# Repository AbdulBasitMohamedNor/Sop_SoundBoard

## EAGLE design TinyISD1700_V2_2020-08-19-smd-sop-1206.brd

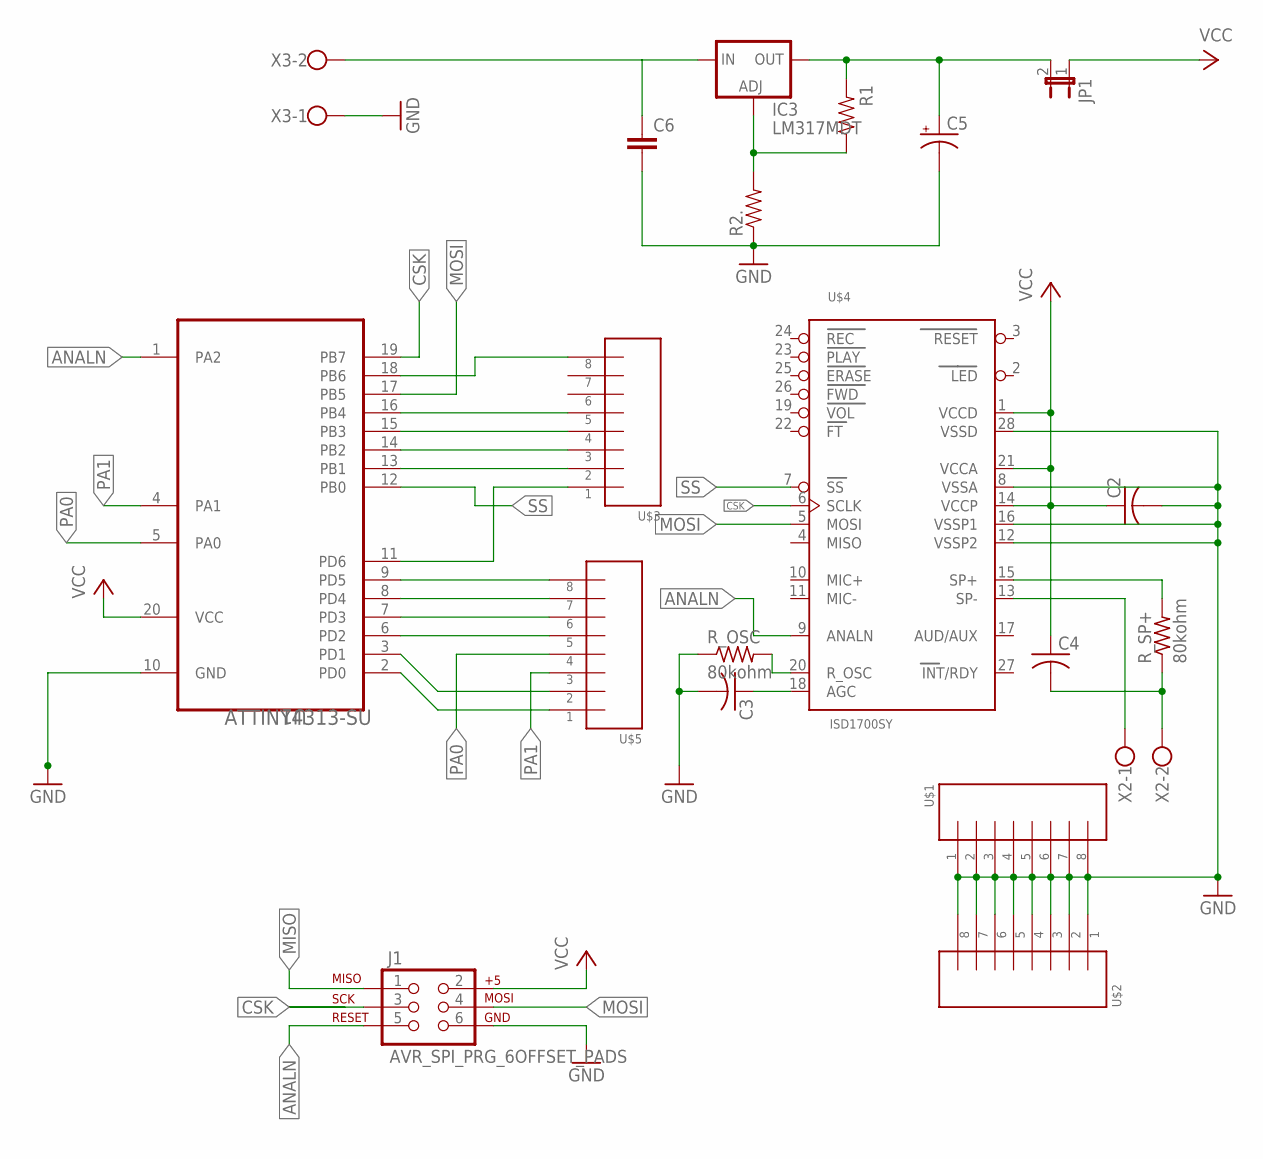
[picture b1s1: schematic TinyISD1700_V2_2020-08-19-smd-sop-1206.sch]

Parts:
C2, C3, C4: C-US050-030X075; C050-030X075
C5: CAP_POL1206; EIA3216
C6: CAP0805; 0805
IC3: LM317MDT; DPACK
J1: AVR_SPI_PRG_6OFFSET_PADS; 2X3_OFFSET
JP1: JP1E; JP1
R1, R2.: RESISTOR; 0805
R_OSC: 80kohm; 0204V
R_SP+: 80kohm; 0204V
U1: ATTINY4313-SU; SOIC127P1032X265-20N
U$1, U$2, U$3, U$5: 8PIN_HEADER; MPN YSDKS128E10
U$4: ISD1700SY; SO28W
X2, X3: W237-102

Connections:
ANALN: J1.5, U1.1 (PA2), U$4.9 (ANALN)
CSK: J1.3, U1.19 (PB7), U$4.6 (SCLK)
GND: C2.2, C3.2, C5.C (-), C6.2, J1.6, R2..1, R_OSC.1, U1.10 (GND), U$1.P$1, U$1.P$2, U$1.P$3, U$1.P$4, U$1.P$5, U$1.P$6, U$1.P$7, U$1.P$8, U$2.P$1, U$2.P$2, U$2.P$3, U$2.P$4, U$2.P$5, U$2.P$6, U$2.P$7, U$2.P$8, U$4.8 (VSSA), U$4.12 (VSSP2), U$4.16 (VSSP1), U$4.28 (VSSD), X3.1
MISO: J1.1
MOSI: J1.4, U1.17 (PB5), U$4.5 (MOSI)
unnamed: R_OSC.2, U$4.20 (R_OSC)
unnamed: U1.13 (PB1), U$3.P$2
unnamed: U1.14 (PB2), U$3.P$3
unnamed: C4.2, R_SP+.1, X2.2
unnamed: C3.1, U$4.18 (AGC)
unnamed: U$4.13 (SP-), X2.1
unnamed: R_SP+.2, U$4.15 (SP+)
unnamed: U1.15 (PB3), U$3.P$4
unnamed: U1.11 (PD6), U$3.P$1
unnamed: U1.9 (PD5), U$5.P$8
unnamed: U1.8 (PD4), U$5.P$7
unnamed: U1.7 (PD3), U$5.P$6
unnamed: U1.6 (PD2), U$5.P$5
unnamed: U1.3 (PD1), U$5.P$2
unnamed: U1.2 (PD0), U$5.P$1
unnamed: C5.A (+), IC3.4 (OUT), JP1.2, R1.2
unnamed: U1.16 (PB4), U$3.P$5
unnamed: C6.1, IC3.3 (IN), X3.2
unnamed: IC3.1 (ADJ), R1.1, R2..2
PA0: U1.5 (PA0), U$5.P$4
PA1: U1.4 (PA1), U$5.P$3
Q: U1.18 (PB6), U$3.P$8
SS: U1.12 (PB0), U$4.7 (SS)
VCC: C2.1, C4.1, J1.2, JP1.1, U1.20 (VCC), U$4.1 (VCCD), U$4.14 (VCCP), U$4.21 (VCCA)

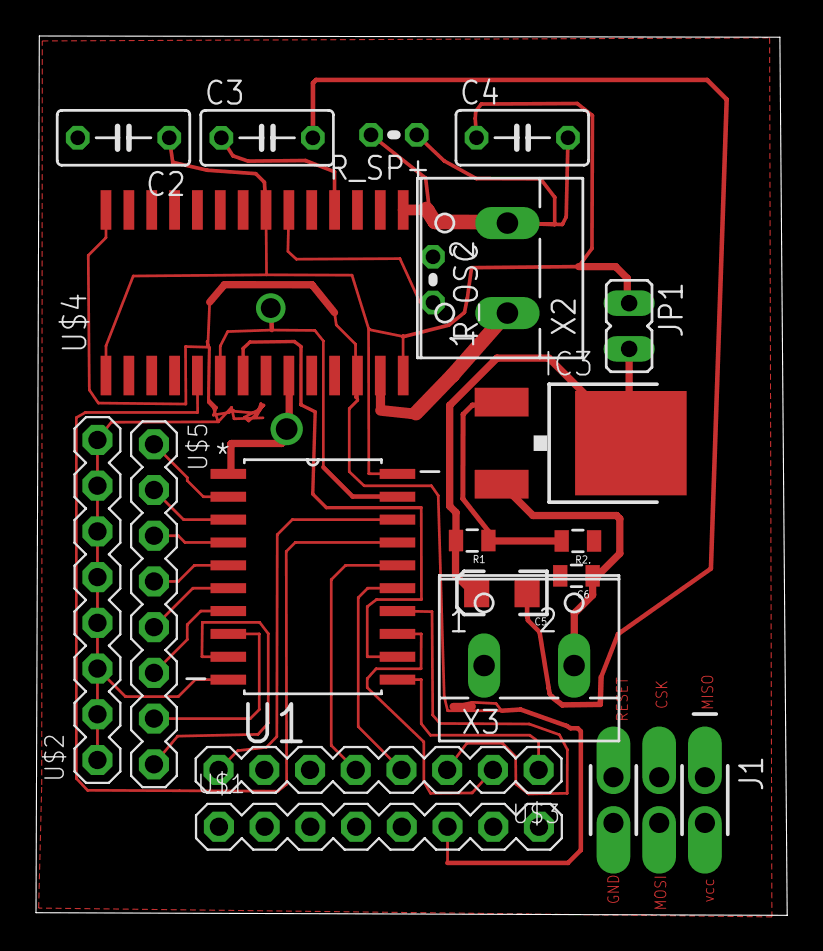
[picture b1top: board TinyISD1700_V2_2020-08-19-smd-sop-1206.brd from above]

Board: 2 copper layers, 41.7 x 48.9 mm, 20 parts (0 on the bottom side), 28 nets.

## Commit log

2020-08-11 tillagd Regulator
2020-08-18 modefied regulator input
2020-08-18 bytt till MDT
2020-08-19 added values
2020-08-19 Resistors changed to 1205 factor
2020-08-21 added css connection
2020-08-25 modded components
2020-08-25 resized board
2020-08-30 pogo probes added
2020-08-31 width modified
